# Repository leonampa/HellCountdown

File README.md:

# HellCountdown 

### 🚩Submitted as a part of [Hack Club Fabricate](https://fabricate.hackclub.com/projects/218)

School days run on a timetable of oddly spaced bells (08:15, 09:00, 09:55, 10:50 ...). Working out "how long is left?" means squinting at a wall clock and doing subtraction in your head, over and over, all day, while trying to watch the teacher's lecture. HellCountdown is a small, battery-powered device that does just one thing: it shows the time left until the next bell on a small OLED screen, for a distraction-free jewel on your desk.

## Features
* The bell times are baked into the firmware, so it just always counts down to whichever bell is next
* A battery-backed real-time clock (RTC) keeps the clock running, even with the power switch off. Wi-Fi is only used once, to set the clock.
* Simple, two-button interface
  * Left: wake the screen. Press again while it's awake to lock it on; press again to unlock.
  * Right: open the custom timer picker. Left subtracts a minute, right adds a minute. Hold to speed up, press both to start the countdown, press right to cancel it.
* Rechargeable: uses a 400 mAh Li-Po, charged over the ESP's USB-C port. 

## Hardware

| Part | Function |
|---|---|
| Waveshare ESP32-S3 Mini | Orchestrates the entire device |
| 0.91" 128x32 SSD1306 OLED (I2C, 0x3C) | Display |
| PCF8563T RTC (I2C, 0x51) + 32.768 kHz crystal | RTC |
| MCP73831 charger | Charger |
| XC6220B331 3.3 V LDO | Supply for the RTC |
| SD0805S040S1R0 Schottky | Stops power backfeeding |
| Li-Po 3.7 V 400 mAh | Battery |
| Slide switch (SPDT) + two tact switches | Power and user buttons |

## Pin map

| GPIO | Function |
|---|---|
| 1 | OLED SCL |
| 2 | OLED SDA |
| 4 | PCF8563 INT (10 kOhm pull-up) |
| 5 | PCF8563 SCL |
| 6 | PCF8563 SDA |
| 12 | Left button (SW3), internal pull-up |
| 13 | Right button (SW2), internal pull-up |

## Configure and install

At the top of the sketch:

- `WIFI_SSID`, `WIFI_PASS`: your Wi-Fi credentials (used only to set the clock).
- `BELLS[]`: the bell times, as "HH:MM" strings.
- `SCREEN_TIMEOUT_MS`: how long the screen stays on.
- `PICK_MIN`, `PICK_MAX`: the custom timer's range in minutes (default 1-99).

Then:

- Install the ESP32 board support in the Arduino IDE (board: ESP32S3 Dev Module, "USB CDC On Boot" enabled).
- Install **RTClib**, **Adafruit SSD1306** and **Adafruit GFX** from the Library Manager.
- Upload over USB-C.

## Bill of materials

| Item  | €/qty  | Qty| €| Notes - Link|
|-------------------------------------------|--------|-------|--------|---------------|
| GRobotronics|  | |  | |
| Waveshare ESP32-S3 Zero – 4MB | 8.20€  | 1  | 8.20€  | https://grobotronics.com/waveshare-esp32-s3-mini-wi-fi-and-bluetooth-5.html|
| Display 0.91" 128x32 OLED Module | 7.40€  | 1  | 7.40€  | https://grobotronics.com/display-0.91-128x32-oled-module.html  |
| Li-Po Battery 3.7V 400mAh Molex 1.25mm | 4.40€  | 1  | 4.40€  | https://grobotronics.com/li-po-battery-3-7v-400mah-molex-1-25mm.html#group_200376ac79e76281b7-2 |
| Led 0805 SMD Red Clear  | 0.10€  | 10 | 1.00€  | https://grobotronics.com/led-0805-smd-red-clear.html  |
| 1kΩ Resistor SMD 0805 1/8W | 0.02€  | 10 | 0.20€  | https://grobotronics.com/resistor-smd-0805-el.html?variation_id=11539|
| 4.7kΩ Resistor SMD 0805 1/8W  | 0.02€  | 10 | 0.20€  | https://grobotronics.com/resistor-smd-0805-el.html?variation_id=11439#group_114396ad377cb0bd9a  |
| 10kΩ Resistor SMD 0805 1/8W| 0.02€  | 10 | 0.20€  | https://grobotronics.com/resistor-smd-0805-el.html?variation_id=11538|
| 32.768 Khz Crystal| 0.25€  | 1  | 0.25€  | https://grobotronics.com/crystal-32-768-khz.html|
| Slide Switch Mini SPDT - 0.3A/30VDC | 0.20€  | 1  | 0.20€  | https://grobotronics.com/mini-spdt-0.3a-30vdc.html |
| Tact switch 6x3mm 4.3mm 2pin PCB | 0.10€  | 2  | 0.20€  | https://grobotronics.com/tact-switch-6x3mm-4.3mm-2pin-pcb.html |
| Pin Header 1x40 Male 2.54 mm Black  | 0.10€  | 1  | 0.10€  | https://grobotronics.com/pin-header-1x40-male-2.54-mm-black.html  |
| Pin Header 1x4 Female 2.54mm  | 0.05€  | 1  | 0.05€  | https://grobotronics.com/pin-header-1x4-female-2.54mm.html  |
| Soldering Wire Brofil 60 16g 1mm | 2.40€  | 1  | 2.40€  | https://grobotronics.com/soldering-wire-brofil-60-16g-1mm.html |
| Creality Ender PLA 1kg – Black [PRORATED] | 12.40€ | 0.010 | 0.12€  | PRORATED - https://grobotronics.com/creality-ender-pla-1-75mm-1kg-black.html  |
| Shipping | 0.00€  | 0  | 2.50€  | BOXNOW|
| TOTAL (EUR) |  | 50 | 27.42€ | |
| |  | |  | |
| Intershop|  | |  | |
| MCP73831T-2ACI/OT / Charger| 1.81€  | 1  | 1.81€  | https://www.inter-shop.gr/shop/hlektronika/%ce%b7%ce%bc%ce%b9%ce%b1%ce%b3%cf%89%ce%b3%ce%bf%ce%af/%ce%bf%ce%bb%ce%bf%ce%ba%ce%bb%ce%b7%cf%81%cf%89%ce%bc%ce%ad%ce%bd%ce%b1-%ce%ba%cf%85%ce%ba%ce%bb%cf%8e%ce%bc%ce%b1%cf%84%ce%b1/%cf%81%cf%85%ce%b8%ce%bc%ce%b9%cf%83%cf%84%ce%ad%cf%82-%cf%84%ce%ac%cf%83%ce%b7%cf%82-%ce%bf%ce%bb%ce%bf%ce%ba%ce%bb%ce%b7%cf%81%cf%89%ce%bc%ce%ad%ce%bd%ce%b1-%ce%ba%cf%85%ce%ba%ce%bb%cf%8e%ce%bc/elegktes-batarion-kai-energeias-kyk-rythmistes-tasis-olokliromena-kyklom/mcp73831t-2aci-otic-pmic-%ce%b5%ce%bb%ce%b5%ce%b3%ce%ba%cf%84%ce%ae%cf%82-%cf%86%cf%8c%cf%81%cf%84%ce%b9%cf%83%ce%b7%cf%82-%cf%83%cf%85%cf%83%cf%83%cf%89%cf%81%ce%b5%cf%85%cf%84%cf%8e%ce%bd-i/|
| XC6220B331MR-G / LDO Reg/tor  | 2.33€  | 1  | 2.33€  | https://www.inter-shop.gr/shop/hlektronika/%ce%b7%ce%bc%ce%b9%ce%b1%ce%b3%cf%89%ce%b3%ce%bf%ce%af/%ce%bf%ce%bb%ce%bf%ce%ba%ce%bb%ce%b7%cf%81%cf%89%ce%bc%ce%ad%ce%bd%ce%b1-%ce%ba%cf%85%ce%ba%ce%bb%cf%8e%ce%bc%ce%b1%cf%84%ce%b1/%cf%81%cf%85%ce%b8%ce%bc%ce%b9%cf%83%cf%84%ce%ad%cf%82-%cf%84%ce%ac%cf%83%ce%b7%cf%82-%ce%bf%ce%bb%ce%bf%ce%ba%ce%bb%ce%b7%cf%81%cf%89%ce%bc%ce%ad%ce%bd%ce%b1-%ce%ba%cf%85%ce%ba%ce%bb%cf%8e%ce%bc/%cf%83%cf%84%ce%b1%ce%b8%ce%b5%cf%81%ce%bf%cf%80%ce%bf%ce%b9%ce%b7%cf%84%ce%ad%cf%82-%ce%b3%cf%81%ce%b1%ce%bc%ce%bc%ce%ae%cf%82-%ce%bf%ce%bb%ce%bf%ce%ba%ce%bb%ce%b7%cf%81-%ce%ba%cf%85%ce%ba%ce%bb/%cf%83%cf%84%ce%b1%ce%b8%ce%b5%cf%81%ce%bf%cf%80%ce%bf%ce%b9%ce%b7%cf%84%ce%ad%cf%82-%cf%84%ce%ac%cf%83%ce%b7%cf%82-%cf%87%cf%89%cf%81%ce%af%cf%82-%cf%81%cf%8d%ce%b8%ce%bc%ce%b9%cf%83%ce%b7-ldo-%cf%83/xc6220b331mr-gic-%cf%83%cf%84%ce%b1%ce%b8%ce%b5%cf%81%ce%bf%cf%80%ce%bf%ce%b9%ce%b7%cf%84%ce%ae%cf%82-%cf%84%ce%ac%cf%83%ce%b7%cf%82-ldo%ce%b3%cf%81%ce%b1%ce%bc%ce%bc%ce%b9%ce%ba%cf%8c%cf%87/ |
| PCF8563T / RTC | 2.76€  | 1  | 2.76€  | https://www.inter-shop.gr/shop/hlektronika/%ce%b7%ce%bc%ce%b9%ce%b1%ce%b3%cf%89%ce%b3%ce%bf%ce%af/%ce%bf%ce%bb%ce%bf%ce%ba%ce%bb%ce%b7%cf%81%cf%89%ce%bc%ce%ad%ce%bd%ce%b1-%ce%ba%cf%85%ce%ba%ce%bb%cf%8e%ce%bc%ce%b1%cf%84%ce%b1/%ce%bf%ce%bb%ce%bf%ce%ba%ce%bb%ce%b7%cf%81%cf%89%ce%bc%ce%ad%ce%bd%ce%b1-%ce%ba%cf%85%ce%ba%ce%bb%cf%8e%ce%bc%ce%b1%cf%84%ce%b1-%cf%80%ce%b5%cf%81%ce%b9%cf%86%ce%b5%cf%81%ce%b5%ce%b9%ce%b1%ce%ba%ce%ac/%ce%ba%cf%85%ce%ba%ce%bb%cf%8e%ce%bc%ce%b1%cf%84%ce%b1-rtc-%ce%bf%ce%bb%ce%bf%ce%ba%ce%bb%ce%b7%cf%81%cf%89%ce%bc%ce%ad%ce%bd%ce%b1-%ce%ba%cf%85%ce%ba%ce%bb%cf%8e%ce%bc%ce%b1%cf%84%ce%b1-%cf%80%ce%b5/pcf8563t-5-518ic-%ce%ba%cf%8d%ce%ba%ce%bb%cf%89%ce%bc%ce%b1-rtc-i2cserial-so8-18%c3%b755v-pcf8563t-5518/ |
| SD0805S040S1R0 / Schottky Diode  | 0.77€  | 1  | 0.77€  | https://www.inter-shop.gr/shop/hlektronika/%ce%b7%ce%bc%ce%b9%ce%b1%ce%b3%cf%89%ce%b3%ce%bf%ce%af/%ce%b4%ce%af%ce%bf%ce%b4%ce%bf%ce%b9/%ce%b4%ce%af%ce%bf%ce%b4%ce%bf%ce%b9-schottky/%ce%b4%ce%af%ce%bf%ce%b4%ce%bf%ce%b9-schottky-smd-%ce%b4%ce%af%ce%bf%ce%b4%ce%bf%ce%b9-schottky-%ce%b4%ce%af%ce%bf%ce%b4%ce%bf%ce%b9-%ce%b7%ce%bc%ce%b9%ce%b1%ce%b3%cf%89%ce%b3%ce%bf%ce%af/sd0805s040s1r0%ce%b4%ce%af%ce%bf%ce%b4%ce%bf%cf%82-%ce%b1%ce%bd%cf%8c%cf%81%ce%b8%cf%89%cf%83%ce%b7%cf%82-schottky-0805-smd-40v-1a-%cf%81%ce%bf%ce%bb%cf%8c%cf%84%ce%b1%ce%b9%ce%bd%ce%af%ce%b1/|
| WR08X5101FTL (5.1kΩ) | 0.19€  | 1  | 0.19€  | https://www.inter-shop.gr/shop/hlektronika/%cf%80%ce%b1%ce%b8%ce%b7%cf%84%ce%b9%ce%ba%ce%ac-%ce%b5%ce%be%ce%b1%cf%81%cf%84%ce%ae%ce%bc%ce%b1%cf%84%ce%b1/%ce%b1%ce%bd%cf%84%ce%b9%cf%83%cf%84%ce%ac%cf%83%ce%b5%ce%b9%cf%82/%ce%b1%ce%bd%cf%84%ce%b9%cf%83%cf%84%ce%ac%cf%83%ce%b5%ce%b9%cf%82-smd-%ce%b1%ce%bd%cf%84%ce%b9%cf%83%cf%84%ce%ac%cf%83%ce%b5%ce%b9%cf%82-%cf%80%ce%b1%ce%b8%ce%b7%cf%84%ce%b9%ce%ba%ce%ac-%ce%b5%ce%be/wr08x5101ftl-%ce%b1%ce%bd%cf%84%ce%af%cf%83%cf%84%ce%b1%cf%83%ce%b7-thick-film-0805-51k%cf%89-125mw-%c2%b11-150v-100ppm-c-wr08x5101ftl/|
| 0805B104K101CT (100nF)  | 0.44€  | 1  | 0.44€  | https://www.inter-shop.gr/shop/hlektronika/%cf%80%ce%b1%ce%b8%ce%b7%cf%84%ce%b9%ce%ba%ce%ac-%ce%b5%ce%be%ce%b1%cf%81%cf%84%ce%ae%ce%bc%ce%b1%cf%84%ce%b1/%cf%80%cf%85%ce%ba%ce%bd%cf%89%cf%84%ce%ad%cf%82/%cf%80%cf%85%ce%ba%ce%bd%cf%89%cf%84%ce%ad%cf%82-mlcc/%cf%80%cf%85%ce%ba%ce%bd%cf%89%cf%84%ce%ad%cf%82-mlcc-smd-%cf%80%cf%85%ce%ba%ce%bd%cf%89%cf%84%ce%ad%cf%82-mlcc/0805b104k101ct-%cf%80%cf%85%ce%ba%ce%bd%cf%89%cf%84%ce%ae%cf%82-%ce%ba%ce%b5%cf%81%ce%b1%ce%bc%ce%b9%ce%ba%cf%8c-100nf-100v-x7r-%c2%b110-0805-0805b104k101ct/|
| 08055D105KAT2A (1uF) | 0.85€  | 2  | 1.69€  | https://www.inter-shop.gr/shop/hlektronika/%cf%80%ce%b1%ce%b8%ce%b7%cf%84%ce%b9%ce%ba%ce%ac-%ce%b5%ce%be%ce%b1%cf%81%cf%84%ce%ae%ce%bc%ce%b1%cf%84%ce%b1/%cf%80%cf%85%ce%ba%ce%bd%cf%89%cf%84%ce%ad%cf%82/%cf%80%cf%85%ce%ba%ce%bd%cf%89%cf%84%ce%ad%cf%82-mlcc/%cf%80%cf%85%ce%ba%ce%bd%cf%89%cf%84%ce%ad%cf%82-mlcc-smd-%cf%80%cf%85%ce%ba%ce%bd%cf%89%cf%84%ce%ad%cf%82-mlcc/08055d105kat2a-%cf%80%cf%85%ce%ba%ce%bd%cf%89%cf%84%ce%ae%cf%82-%ce%ba%ce%b5%cf%81%ce%b1%ce%bc%ce%b9%ce%ba%cf%8c-mlcc-1uf-50v-x5r-%c2%b110-smd-0805-180mm-08055d105kat2a/|
| EMK212B7475KG (4.7uF)| 0.85€  | 2  | 1.70€  | https://www.inter-shop.gr/shop/hlektronika/%cf%80%ce%b1%ce%b8%ce%b7%cf%84%ce%b9%ce%ba%ce%ac-%ce%b5%ce%be%ce%b1%cf%81%cf%84%ce%ae%ce%bc%ce%b1%cf%84%ce%b1/%cf%80%cf%85%ce%ba%ce%bd%cf%89%cf%84%ce%ad%cf%82/%cf%80%cf%85%ce%ba%ce%bd%cf%89%cf%84%ce%ad%cf%82-mlcc/%cf%80%cf%85%ce%ba%ce%bd%cf%89%cf%84%ce%ad%cf%82-mlcc-smd-%cf%80%cf%85%ce%ba%ce%bd%cf%89%cf%84%ce%ad%cf%82-mlcc/emk212b7475kg-t-%cf%80%cf%85%ce%ba%ce%bd%cf%89%cf%84%ce%ae%cf%82-%ce%ba%ce%b5%cf%81%ce%b1%ce%bc%ce%b9%ce%ba%cf%8c-mlcc-47uf-16v-x7r-%c2%b110-smd-0805-2x125mm-emk212b7475kg-t/ |
| CC0805KKX5R5BB226 (22uF)| 0.97€  | 1  | 0.97€  | https://www.inter-shop.gr/shop/hlektronika/%cf%80%ce%b1%ce%b8%ce%b7%cf%84%ce%b9%ce%ba%ce%ac-%ce%b5%ce%be%ce%b1%cf%81%cf%84%ce%ae%ce%bc%ce%b1%cf%84%ce%b1/%cf%80%cf%85%ce%ba%ce%bd%cf%89%cf%84%ce%ad%cf%82/%cf%80%cf%85%ce%ba%ce%bd%cf%89%cf%84%ce%ad%cf%82-mlcc/%cf%80%cf%85%ce%ba%ce%bd%cf%89%cf%84%ce%ad%cf%82-mlcc-smd-%cf%80%cf%85%ce%ba%ce%bd%cf%89%cf%84%ce%ad%cf%82-mlcc/cc0805kkx5r5bb226-%cf%80%cf%85%ce%ba%ce%bd%cf%89%cf%84%ce%ae%cf%82-%ce%ba%ce%b5%cf%81%ce%b1%ce%bc%ce%b9%ce%ba%cf%8c-mlcc-22uf-63v-x5r-%c2%b110-smd-0805-cc0805kkx5r5bb226/  |
| Shipping | 2.99€  | 1  | 2.99€  | ACS Lockers |
| VAT|  | | 3.76€  | |
| TOTAL (EUR) |  | 12 | 19.41€ | |
| |  | |  | |
| JLCPCB|  | |  | |
| PCB, 34*41mm, 5pcs| 3.62€  | 1  | 3.62€  | |
| Shipping | 5.49€  | 1  | 5.49€  | |
| VAT, Duties | 7.23€  | 1  | 7.23€  | |
| TOTAL (EUR) |  | | 16.34€ | |
| |  | |  | |
| GRAND TOTAL (EUR) |  | | 63.17€ | (about 69.49 USD, considering 1€=$1.10 (as of 15 Nov) |

## Features that are Work In Progress

- **Not yet tested as an assembled device.** The firmware logic isn't verified with the other components yet.
- **No deep sleep yet.** "Sleep" currently turns only the OLED off; the ESP keeps running. 

## AI Disclosure

This project was built with help from an AI assistant, that drove the development of the firmware, and reviewed the PCB wiring.

## License

[MIT](LICENSE)

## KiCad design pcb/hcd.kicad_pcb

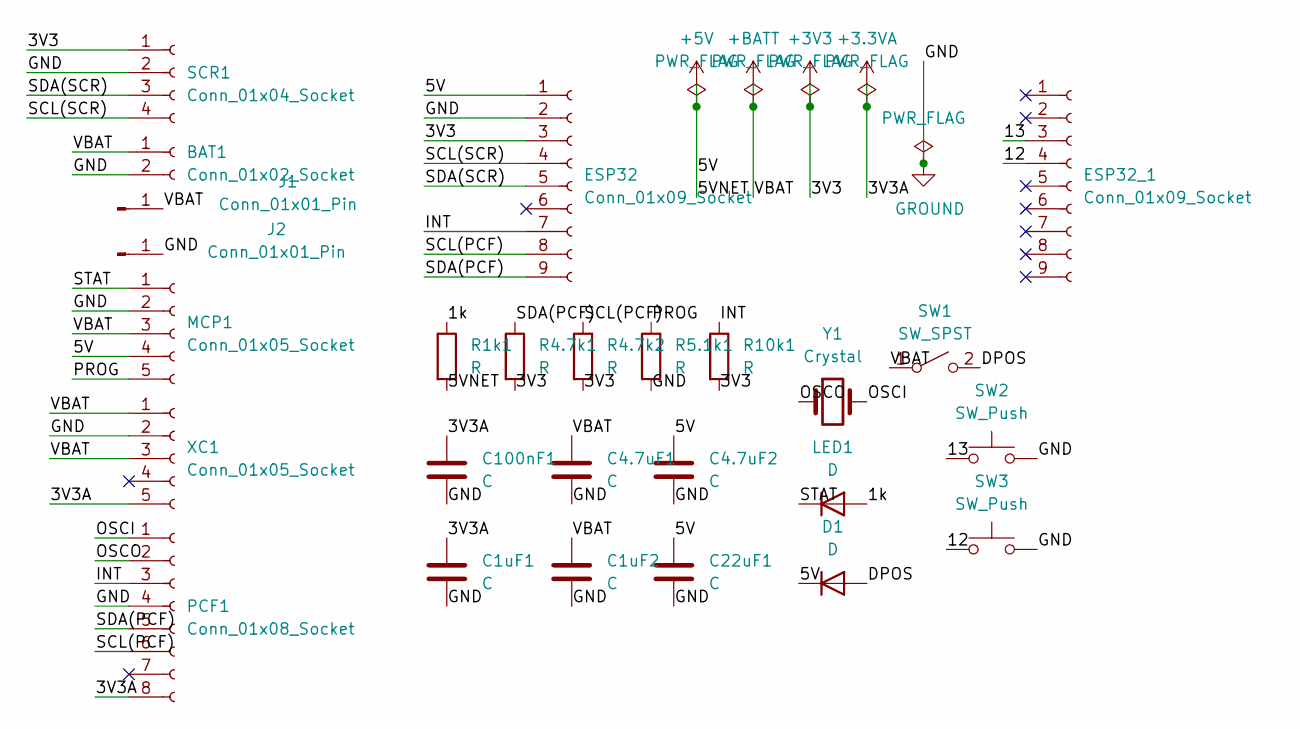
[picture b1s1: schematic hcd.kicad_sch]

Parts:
BAT1: Conn_01x02_Socket
C1uF1, C1uF2, C4.7uF1, C4.7uF2, C22uF1, C100nF1: C
D1: D
ESP32, ESP32_1: Conn_01x09_Socket
J1, J2: Conn_01x01_Pin
LED1: D
MCP1: Conn_01x05_Socket
PCF1: Conn_01x08_Socket
R1k1, R4.7k1, R4.7k2, R5.1k1, R10k1: R
SCR1: Conn_01x04_Socket
SW1: SW_SPST; SW_NKK_GW12LJP
SW2, SW3: SW_Push
XC1: Conn_01x05_Socket
Y1: Crystal

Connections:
+3.3VA: C1uF1.1, C100nF1.1, PCF1.8, XC1.5
+3V3: ESP32.3, R4.7k1.2, R4.7k2.2, R10k1.2, SCR1.1
+5V: C4.7uF2.1, C22uF1.1, D1.1 (K), ESP32.1, MCP1.4, R1k1.2
+BATT: BAT1.1, C1uF2.1, C4.7uF1.1, J1.1 (Pin_1_1), MCP1.3, SW1.1 (A), XC1.1, XC1.3
/1k: LED1.2 (A), R1k1.1
/12: ESP32_1.4, SW3.1
/13: ESP32_1.3, SW2.1
/DPOS: D1.2 (A), SW1.2 (B)
/INT: ESP32.7, PCF1.3, R10k1.1
/OSCI: PCF1.1, Y1.2
/OSCO: PCF1.2, Y1.1
/PROG: MCP1.5, R5.1k1.1
/SCL(PCF): ESP32.8, PCF1.6, R4.7k2.1
/SCL(SCR): ESP32.4, SCR1.4
/SDA(PCF): ESP32.9, PCF1.5, R4.7k1.1
/SDA(SCR): ESP32.5, SCR1.3
/STAT: LED1.1 (K), MCP1.1
GROUND: BAT1.2, C1uF1.2, C1uF2.2, C4.7uF1.2, C4.7uF2.2, C22uF1.2, C100nF1.2, ESP32.2, J2.1 (Pin_1_1), MCP1.2, PCF1.4, R5.1k1.2, SCR1.2, SW2.2, SW3.2, XC1.2

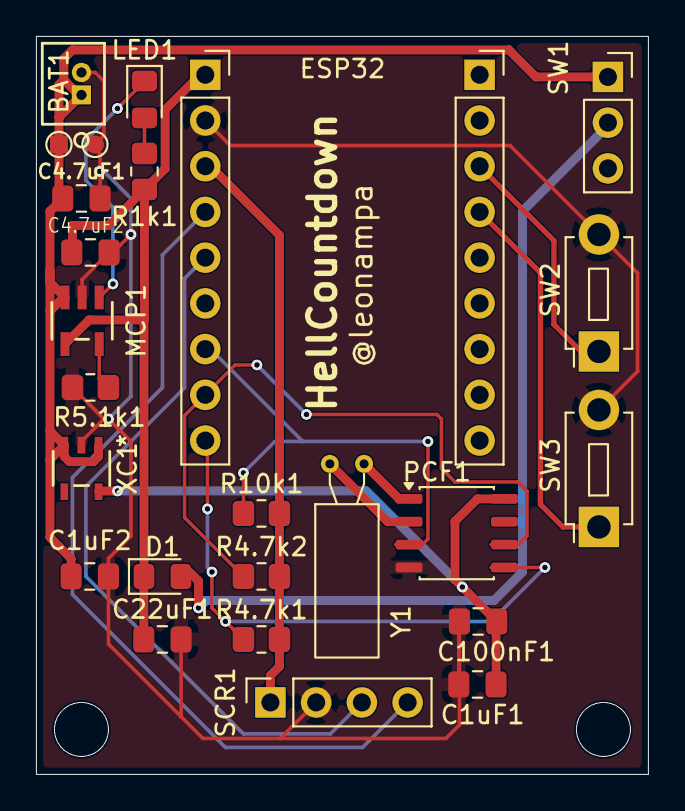
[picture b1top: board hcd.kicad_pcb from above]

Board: 2 copper layers, 34.0 x 41.0 mm, 26 parts (0 on the bottom side), 18 nets.

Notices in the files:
parts and their libraries:
Copyright 2016 Accelerated Designs. All rights reserved.
